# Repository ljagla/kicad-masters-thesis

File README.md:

# kicad-masters-thesis
Repozitář souborů návrhu DPS diplomové práce na téma: "Adaptace digitálního předzkreslovače pro linearizaci zesilovačů s použitím komparátoru" v prostředí KiCad.

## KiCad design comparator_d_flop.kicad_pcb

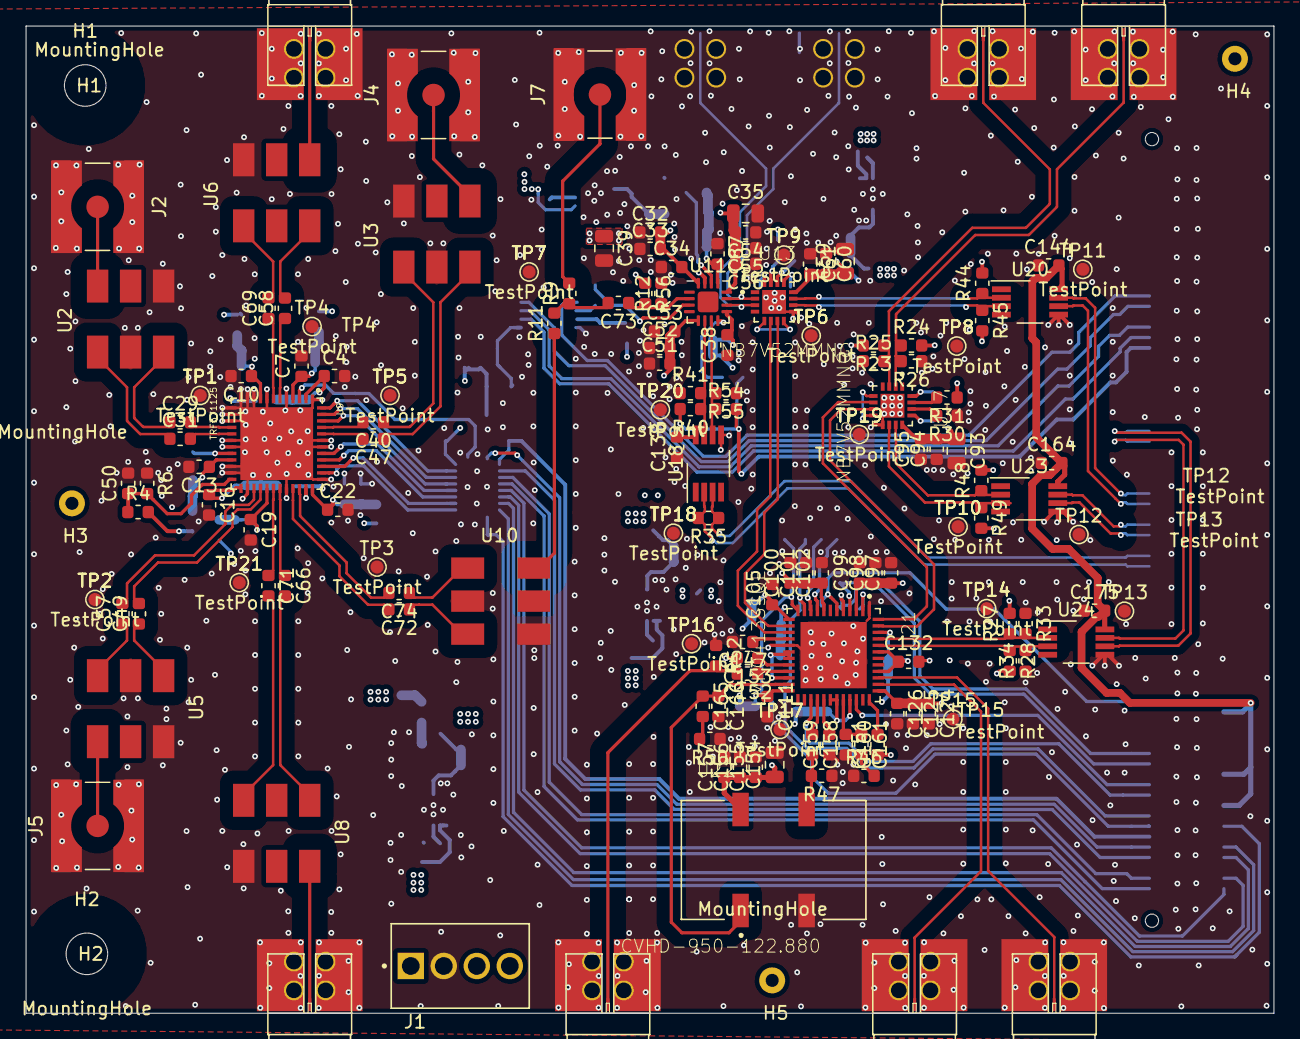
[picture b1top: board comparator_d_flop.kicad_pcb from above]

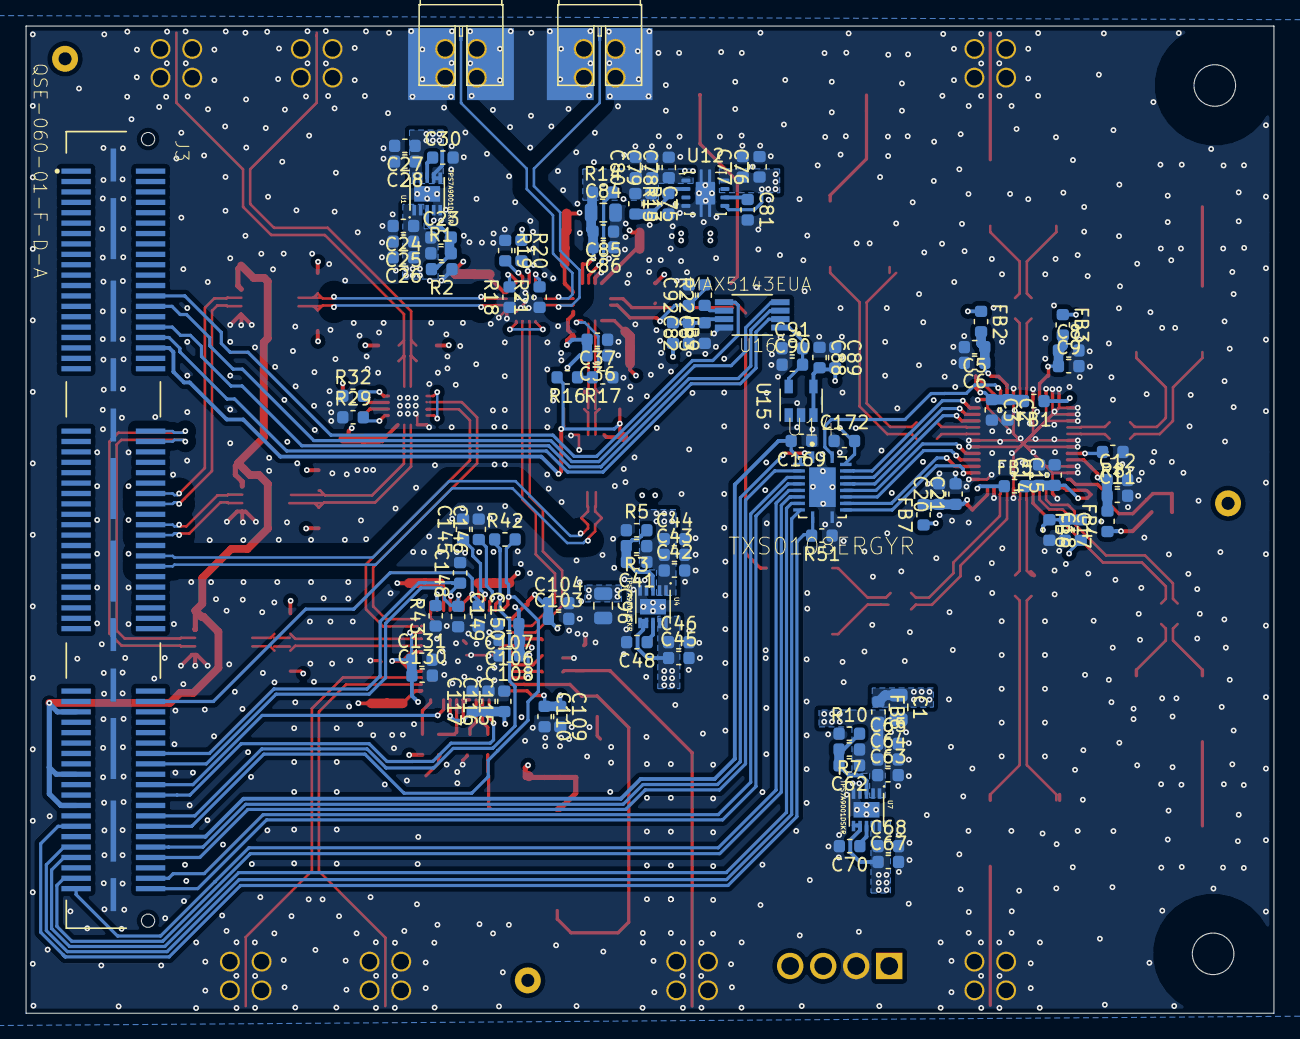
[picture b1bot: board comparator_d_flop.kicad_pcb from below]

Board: 4 copper layers, 96.0 x 75.9 mm, 269 parts (116 on the bottom side), 147 nets.

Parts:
C1, C35, C39, C59, C84, C93, C96, C154: 47u; C_0805_2012Metric
C2, C5, C8, C11, C14, C17, C20, C25, C32, C36, C43, C51, C54, C60, C64, C79, C82, C85, C88, C90, C94, C97, C100, C103, C106, C109, C115, C124, C130, C151, C153, C155: 1u; C_0603_1608Metric
C3, C6, C9, C12, C15, C18, C21, C23, C26, C29, C31, C33, C37, C40, C41, C44, C47, C49, C52, C55, C57, C61, C62, C65, C72, C73, C74, C75, C80, C81, C83, C86, C89, C91, C95, C98, C101, C104, C107, C110, C116, C125, C131, C138, C144, C152, C156, C164, C169, C172, C175: 10n; C_0603_1608Metric
C4, C7, C10, C13, C16, C19, C22, C34, C38, C53, C56, C87, C99, C102, C105, C108, C111, C117, C126, C132, C157: 100p; C_0603_1608Metric
C24, C27, C42, C45, C63, C67, C76, C78, C145: 10u; C_0603_1608Metric
C28, C30, C46, C48, C50, C68, C70, C77, C146, C158, C159: 100n; C_0603_1608Metric
C58, C66, C69, C71: 10p; C_0603_1608Metric
C92: 1n; C_0603_1608Metric
C147: 470n; C_0603_1608Metric
C148, C149, C150: 33p; C_0603_1608Metric
C160, C161, C165, C166: PLL; C_0603_1608Metric
FB1, FB2, FB3, FB4, FB5, FB6, FB7, FB8, FB9: 120; R_0603_1608Metric
H1, H2: MountingHole; MountingHole_3.2mm_M3
H3, H4, H5: MountingHole; Crocodile_hole
J1: Conn_01x04_Female; TE_282834-4
J2, J4, J5, J7: Conn_Coaxial; SMA_Amphenol_132134-10_Vertical
J3: QSE-060-01-F-D-A; SAMTEC_QSE-060-01-L-D-A
J6, J8, J9, J10, J11, J12, J13, J14, J15: Conn_Coaxial; 901-10510-2
R1, R4: 4k7; R_0603_1608Metric
R2: 2k2; R_0603_1608Metric
R3: 6k2; R_0603_1608Metric
R5, R6, R14: 2k; R_0603_1608Metric
R7: 27k; R_0603_1608Metric
R8, R51: 30k; R_0603_1608Metric
R9, R40, R41, R54, R55: OPEN; R_0603_1608Metric
R10: 5k1; R_0603_1608Metric
R11, R42: 0R; R_0603_1608Metric
R12, R18, R19, R20, R21, R29, R30, R31, R32, R35, R56: 100R; R_0603_1608Metric
R13: 39k; R_0603_1608Metric
R15: 12k; R_0603_1608Metric
R16, R23, R24: 240R; R_0603_1608Metric
R17, R25, R26: 62R; R_0603_1608Metric
R22: 1k5; R_0603_1608Metric
R27, R28: 130R; R_0603_1608Metric
R33, R34: 82R; R_0603_1608Metric
R43, R44, R45, R47, R48, R49, R52: 51R; R_0603_1608Metric
R46, R50: PLL; R_0603_1608Metric
TP1, TP2, TP3, TP4, TP5, TP6, TP7, TP8, TP9, TP10, TP11, TP12, TP13, TP14, TP15, TP16, TP17, TP18, TP19, TP20, TP21: TestPoint; TestPoint_Pad_D1.0mm
U1, U4, U7: TPS7A9001DSKR; SON50P250X250X80-11N
U2, U3, U5, U10: ADT2-1T+; Minicircuits_A_type
U6, U8: ADTL2-18+; Minicircuits_A_type
U9: TRF371125; QFP50P700X700X90-49N
U11: ADCMP582; LFCSP-16-1EP_3x3mm_P0.5mm_EP1.6x1.6mm
U12: TPS7A3001DRBR; VSON-10-1EP_3x3mm_P0.5mm_EP1.5x1.75mm
U13, U17: NB7V52MMNG; QFN3x3x0.5P-17N
U14: TXS0108ERGYR; QFN50P450X350X100-21N
U15: LM4132AMF-3.0; SOT-23-5
U16: MAX5143EUA; SOP65P490X110-8N
U18: SN65LVDS101DGK; VSSOP-8_3.0x3.0mm_P0.65mm
U20, U23, U24: SN65LVDS100DGKR; VSSOP-8_3.0x3.0mm_P0.65mm
U21: LMK04133SQE; QFN50P700X700X80-49N
U22: CVHD-950-122.880; OSCSC508P1420X914X530-4N

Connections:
+2.5V_FPGA: C138.2, J3.36, R16.2, R40.2, R54.2, U18.8
+2V5: C23.1, C24.1, C25.1, C26.1, C35.1, C36.2, C37.2, C38.2, C54.2, C55.2, C56.2, C59.1, C60.2, C61.2, C93.1, C94.2, C95.2, R1.1, R20.1, R23.2, R24.2, R31.1, R44.2, R45.2, R48.2, R49.2, U1.1, U1.2, U11.9, U11.12, U13.12, U17.12
+3.3V_FPGA_LSHIFT: C169.2, J3.110, U14.2
+3.3V_FPGA_TRANS: C144.2, C164.2, C175.2, J3.85, J3.97, J3.103, U20.8, U23.8, U24.8
+3V3: C41.1, C42.1, C43.1, C44.1, C96.1, C97.1, C98.1, C99.1, C100.1, C101.1, C102.1, C103.1, C104.1, C105.1, C106.1, C107.1, C108.1, C109.1, C110.1, C111.1, C115.1, C116.1, C117.1, C124.1, C125.1, C126.1, C130.1, C131.1, C132.1, C151.1, C154.1, C155.1, C156.1, C157.1, FB9.2, R3.1, R27.2, R28.2, U4.1, U4.2, U21.3, U21.8, U21.13, U21.18, U21.19, U21.22, U21.24, U21.30, U21.31, U21.33, U21.37, U21.40, U21.43, U21.46, U22.4
+3V3_DAC: C82.2, C83.2, FB9.1, U16.7
+5V: C32.2, C33.2, C34.2, C39.1, C51.2, C52.2, C53.2, C62.1, C63.1, C64.1, C65.1, C88.2, C89.2, C172.2, FB8.2, R7.1, R56.1, U7.1, U7.2, U11.5, U11.16, U14.19, U15.3, U15.4
+5V_MIX: C1.1, FB1.1, FB2.1, FB3.1, FB4.1, FB5.1, FB6.1, FB7.1, FB8.1, R4.2
+VDC_1: C27.1, C28.1, C45.1, C46.1, J1.4, U1.6, U1.7, U1.9, U1.10, U4.6, U4.7, U4.9, U4.10
+VDC_2: C67.1, C68.1, J1.1, U7.6, U7.7, U7.9, U7.10
-5V: C75.1, C78.1, C79.1, C80.1, C84.1, C85.2, C86.2, C87.2, R13.1, R14.1, U11.13, U12.1
-VDC: C76.1, C77.1, J1.3, U12.5, U12.8
/BBI_N: C74.2, U9.34
/BBI_P: C72.2, U9.33
/BBQ_N: C57.2, U9.27
/BBQ_P: C49.2, U9.28
/Bias: C151.2, U21.36
/CLKin0: C153.1, U21.20
/CLKin*: C152.1, U21.21
/CLOCK: U9.48, U14.18
/CPout1: C165.1, C166.1, U21.23, U22.1
/CPout2: C160.1, C161.1, U21.32
/D2IN_N: J12.1, R23.1, R25.2, U17.3
/D2IN_P: J10.1, R24.1, R26.2, U17.2
/DACOUT: R22.1, U16.6
/DACREF: C90.2, C91.2, U15.5, U16.1
/DATA: U9.47, U14.17
/FPGA_N: R28.1, R34.2, U21.44, U24.3
/FPGA_P: R27.1, R33.2, U21.45, U24.2
/Fout: R43.2, U21.2
/GAIN0: U9.41, U14.15
/GAIN1: U9.40, U14.14
/GAIN2: U9.39, U14.13
/HYS: R14.2, U11.14
/I_N: C74.1, U10.4
/I_P: C72.1, U10.6
/LDObyp1: C145.1, U21.9
/LDObyp2: C146.1, U21.10
/LE_N: R40.1, R41.2, U11.6, U18.7
/LE_P: R54.1, R55.2, U11.7, U18.6
/LOIN: C71.1, U9.30
/LOIP: C66.1, U9.31
/LO_N: C71.2, U8.6
/LO_P: C66.2, U8.4
/MIXIN: C47.2, U9.44
/MIXINN: C69.1, U9.7
/MIXINP: C58.1, U9.6
/MIXIP: C40.2, U9.45
/MIXQ_N: C31.2, U9.17
/MIXQ_P: C29.2, U9.16
/MIX_N: C69.2, U6.4
/MIX_P: C58.2, U6.6
/MI_N: C47.1, U3.6
/MI_P: C40.1, U3.4
/MQ_N: C31.1, U2.4
/MQ_P: C29.1, U2.6
/OSCin: C158.1, U21.28
/OSCin*: C159.2, U21.29
/QCOMP_N: J9.1, U11.10, U13.3
/QCOMP_P: J11.1, U11.11, U13.2
/Q_N: C57.1, U5.6
/Q_P: C49.1, U5.4
/R1: R19.2, U13.14
/R1*: R20.2, U13.15
/R2: R30.2, U17.14
/R2*: R31.2, U17.15
/READBACK: U9.38, U14.12
/REXT: R8.2, U9.20
/STROBE: U9.46, U14.16
/VCXODAC_N: J14.1, U21.38
/VCXODAC_P: J13.1, U21.39
/VN: C92.1, R22.2, U11.3
/VP: C73.1, R12.1, R56.2, U11.2
/VTR: R18.2, U13.13
/VTR1*: R21.2, U13.16
/VTR2: R29.2, U17.13
/VTR2*: R32.2, U17.16
/VTTCO: R16.1, R17.2, U11.8
CHIP_EN: J3.112, U14.1
CLK_DAC: J3.32, U16.3
CLK_LOS: J3.100, U21.34
CLKuWIRE: C148.1, J3.94, U21.4
CS_DAC: J3.34, U16.2
D1CLK_N: U13.7, U21.14
D1CLK_P: U13.6, U21.15
D1QOUT_N: J3.56, U20.6
D1QOUT_P: J3.54, U20.7
D1Q_N: R45.1, U13.10, U20.3
D1Q_P: R44.1, U13.11, U20.2
D2CLK_N: U17.7, U21.47
D2CLK_P: U17.6, U21.48
D2QOUT_N: J3.62, U23.6
D2QOUT_P: J3.60, U23.7
D2Q_N: R49.1, U17.10, U23.3
D2Q_P: R48.1, U17.11, U23.2
DAC_CLR: J3.26, U16.5
DATA_DAC: J3.28, U16.4
DATAuWIRE: C149.1, J3.96, U21.5
FPGACLK_N: J3.44, U24.7
FPGACLK_P: J3.42, U24.6
FPGALE_N: J3.66, R35.1, U18.3
FPGALE_P: J3.68, R35.2, U18.2
GAIN_B0: J3.119, U14.6
GAIN_B1: J3.117, U14.7
GAIN_B2: J3.113, U14.8
GND: C1.2, C2.2, C3.2, C4.2, C5.2, C6.2, C7.2, C8.2, C9.2, C10.2, C11.2, C12.2, C13.2, C14.2, C15.2, C16.2, C17.2, C18.2, C19.2, C20.2, C21.2, C22.2, C24.2, C25.2, C26.2, C27.2, C28.2, C30.2, C32.1, C33.1, C34.1, C35.2, C36.1, C37.1, C38.1, C39.2, C42.2, C43.2, C44.2, C45.2, C46.2, C48.2, C50.2, C51.1, C52.1, C53.1, C54.1, C55.1, C56.1, C59.2, C60.1, C61.1, C63.2, C64.2, C65.2, C67.2, C68.2, C70.2, C76.2, C77.2, C78.2, C79.2, C80.2, C81.2, C82.1, C83.1, C84.2, C85.1, C86.1, C87.1, C88.1, C89.1, C90.1, C91.1, C92.2, C93.2, C94.1, C95.1, C96.2, C97.2, C98.2, C99.2, C100.2, C101.2, C102.2, C103.2, C104.2, C105.2, C106.2, C107.2, C108.2, C109.2, C110.2, C111.2, C115.2, C116.2, C117.2, C124.2, C125.2, C126.2, C130.2, C131.2, C132.2, C138.1, C144.1, C145.2, C146.2, C147.2, C148.2, C149.2, C150.2, C153.2, C154.2, C155.2, C156.2, C157.2, C159.1, C160.2, C164.1, C166.2, C169.1, C172.1, C175.1, J1.2, J2.2, J3.121, J3.122, J3.123, J3.124, J3.125, J3.126, J3.127, J3.128, J3.129, J3.130, J3.131, J3.132, J4.2, J5.2, J6.2, J7.2, J8.2, J9.2, J10.2, J11.2, J12.2, J13.2, J14.2, J15.2, R2.1, R5.1, R6.1, R8.1, R10.1, R12.2, R15.1, R17.1, R18.1, R19.1, R21.1, R25.1, R26.1, R29.1, R30.1, R32.1, R33.1, R34.1, R41.1, R43.1, R46.1, R47.1, R50.1, R51.1, R52.1, R55.1, TP1.1, TP2.1, TP3.1, TP4.1, TP5.1, TP6.1, TP7.1, TP8.1, TP9.1, TP10.1, TP11.1, TP12.1, TP13.1, TP14.1, TP15.1, TP16.1, TP17.1, TP18.1, TP19.1, TP20.1, TP21.1, U1.4, U1.5, U1.11, U2.1, U2.5, U3.3, U3.5, U4.4, U4.5, U4.11, U5.3, U5.5, U6.3, U7.4, U7.5, U7.11, U8.1, U9.1, U9.5, U9.8, U9.10, U9.11, U9.12, U9.13, U9.14, U9.15, U9.18, U9.19, U9.22, U9.23, U9.26, U9.32, U9.35, U9.37, U9.42, U9.43, U9.49, U10.1, U10.5, U11.15, U12.4, U12.9, U13.9, U13.17, U14.11, U14.21, U15.2, U16.8, U17.9, U17.17, U18.5, U20.5, U21.1, U21.17, U21.49, U22.2, U23.5, U24.5
GOE: J3.106, R42.1, U21.11
LD: J3.108, R42.2, U21.12
LEuWIRE: C150.1, J3.84, U21.6
unnamed: C23.2, R1.2, R2.2, U1.3
unnamed: C30.1, U1.8
unnamed: C41.2, R3.2, R5.2, U4.3
unnamed: C48.1, U4.8
unnamed: C50.1, R4.1, R6.2, U9.24
unnamed: C62.2, R7.2, R10.2, U7.3
unnamed: C70.1, U7.8
unnamed: C73.2, R9.1, R11.2
unnamed: C75.2, R13.2, R15.2, U12.2
unnamed: C81.1, U12.6
unnamed: C147.1, U21.16
unnamed: C152.2, J15.1, R52.2
unnamed: C158.2, R47.2, U22.3
unnamed: C161.2, R46.2
unnamed: C165.2, R50.2
unnamed: J2.1, U2.3
unnamed: J4.1, U3.1
unnamed: J5.1, U5.1
unnamed: J6.1, U6.1
unnamed: J7.1, R9.2
unnamed: J8.1, U8.3
unnamed: R11.1, U10.3
unnamed: U13.5, U13.8
unnamed: U9.3, U14.20
unnamed: U17.5, U17.8
OE: J3.107, R51.2, U14.10
SPI_CLK: J3.114, U14.3
SPI_DATA: J3.118, U14.4
SPI_READBACK: J3.111, U14.9
SPI_STROBE: J3.120, U14.5
SYNC: J3.102, U21.27
VCCBBI: C20.1, C21.1, C22.1, FB7.2, U9.36
VCCBBQ: C14.1, C15.1, C16.1, FB5.2, U9.25
VCCBIAS: C11.1, C12.1, C13.1, FB4.2, U9.21
VCCDIG: C2.1, C3.1, C4.1, FB1.2, U9.2
VCCLO: C17.1, C18.1, C19.1, FB6.2, U9.29
VCCMIX1: C5.1, C6.1, C7.1, FB2.2, U9.4
VCCMIX2: C8.1, C9.1, C10.1, FB3.2, U9.9

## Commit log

2020-03-29 manufactured version of PCB
